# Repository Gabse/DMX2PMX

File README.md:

DMX2PMX
=
DMX512 to Dual PMX Converter

=
This simple device converts a standard DMX512 Signal into two Pulsar PMX signals.

It lets you reuse your old Pulsar/ClayPaky gear with almost any standard DMX controller on the market.

The device has 2 independent outputs giving the user the posibility to split the incomming signal into two outputs 
to achieve a faster update rate than by using a single PMX channel only (≈2,08ms per channel in 7 bit mode).

The number of desired channels per output and the bit mode can be modified in the sourcecode file.

9 Dip Swithes make it possible to set a DMX start address, in order to expand existing DMX universes.

The opto-isolated input helps to avoid ground loops between the DMX and the PMX side.

Please also visit my [Blog Post](https://gabsesblog.blogspot.com/2021/07/clay-packy-golden-scan.html) for additional information.

Safety information / disclaimer:
=

This device SHOULD NOT be used with anything safety related. It is only meant to control dimmer packs and other lighting fixtures.
It is not allowed to be used with moving stage parts, pyros and similar SFX. Doing so will happen at your OWN RISK!

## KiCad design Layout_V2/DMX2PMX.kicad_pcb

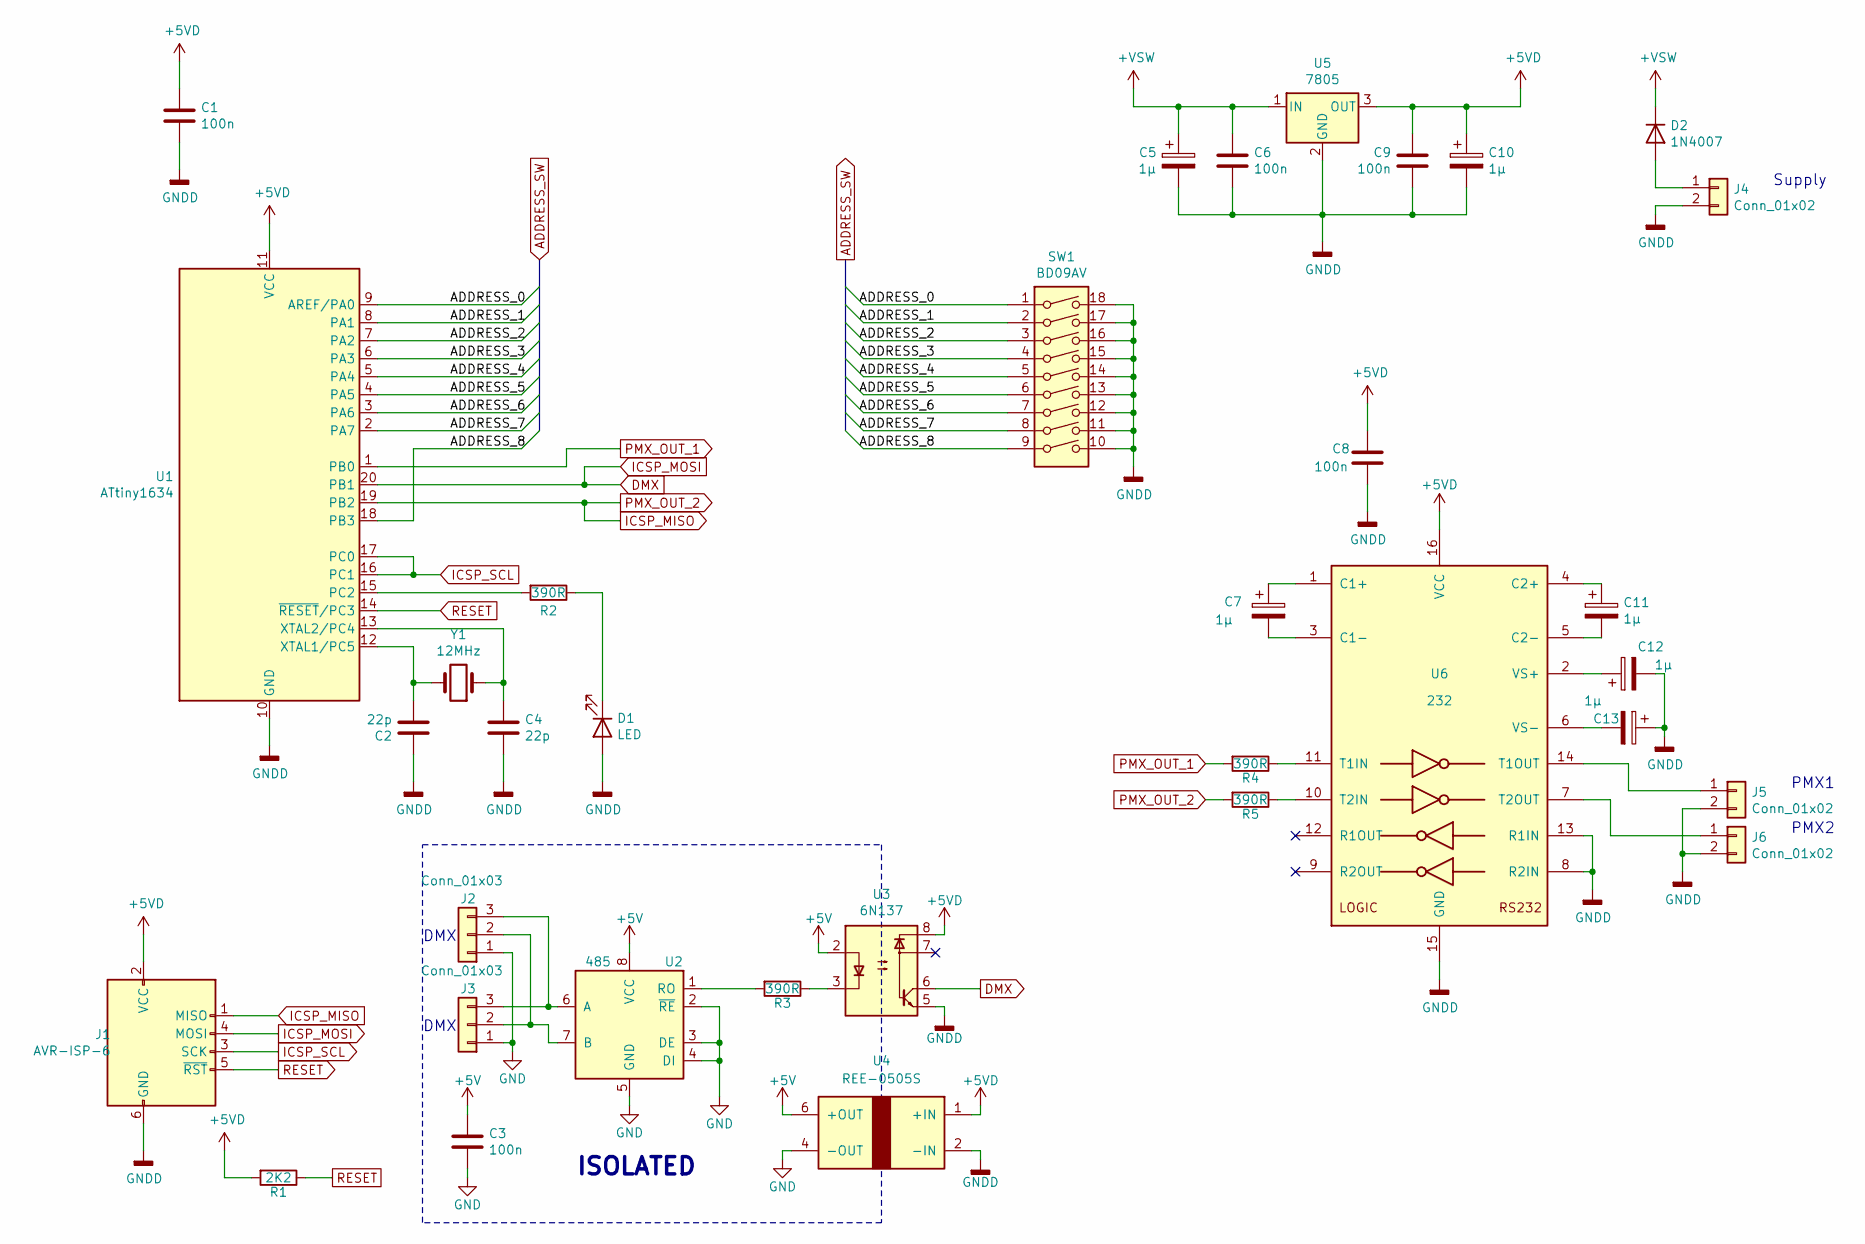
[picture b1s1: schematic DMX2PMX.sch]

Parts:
C1, C3, C6, C8, C9: 100n; C_Disc_D3.0mm_W1.6mm_P2.50mm; MPN C315C103K5R5TA
C2, C4: 22p; C_Disc_D3.0mm_W1.6mm_P2.50mm; MPN C315C229D2G5TA
C5, C7, C10, C11, C12, C13: 1µ; CP_Radial_D6.3mm_P2.50mm; MPN UPS2D010MED
D1: LED; LED_D5.0mm; MPN TLHY5400-AS12Z
D2: 1N4007; D_DO-15_P12.70mm_Horizontal; MPN 1N4007-E3/54
J1: AVR-ISP-6; PinHeader_2x03_P2.54mm_Vertical; MPN 67996-206HLF
J2, J3: Conn_01x03; PinHeader_1x03_P2.54mm_Vertical; MPN 90120-0763
J4, J5, J6: Conn_01x02; PinHeader_1x02_P2.54mm_Vertical; MPN 90120-0762
R1: 2K2; R_Axial_DIN0309_L9.0mm_D3.2mm_P12.70mm_Horizontal; MPN MBA02040C2201FCT00
R2, R3, R4, R5: 390R; R_Axial_DIN0309_L9.0mm_D3.2mm_P12.70mm_Horizontal; MPN MBA02040C3900FC100
SW1: BD09AV; MPN BD09AV
U1: ATtiny1634; SOIC-20W_7.5x12.8mm_Pitch1.27mm; MPN ATTINY1634-SU
U2: 485; DIP-8_W7.62mm_Socket_LongPads; MPN SN75176BP
U3: 6N137; DIP-8_W7.62mm_Socket_LongPads; MPN 6N137
U4: REE-0505S; RECOM-REE-0505S; MPN REE-0505S
U5: 7805; TO-220-3_Vertical; MPN L7805ABP
U6: 232; DIP-16_W7.62mm_Socket_LongPads; MPN MAX232N
Y1: 12MHz; Crystal_HC49-4H_Vertical; MPN LF XTAL003215

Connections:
+5V: C3.1, U2.8 (VCC), U3.2, U4.6 (+OUT)
+5VD: C1.1, C8.1, C9.1, C10.1, J1.2 (VCC), R1.2, U1.11 (VCC), U3.8, U4.1 (+IN), U5.3 (OUT), U6.16 (VCC)
+VSW: C5.1, C6.1, D2.1 (K), U5.1 (IN)
/ADDRESS_0: SW1.1, U1.9 (AREF/PA0)
/ADDRESS_1: SW1.2, U1.8 (PA1)
/ADDRESS_2: SW1.3, U1.7 (PA2)
/ADDRESS_3: SW1.4, U1.6 (PA3)
/ADDRESS_4: SW1.5, U1.5 (PA4)
/ADDRESS_5: SW1.6, U1.4 (PA5)
/ADDRESS_6: SW1.7, U1.3 (PA6)
/ADDRESS_7: SW1.8, U1.2 (PA7)
/ADDRESS_8: SW1.9, U1.18 (PB3)
DMX: J1.4 (MOSI), U1.20 (PB1), U3.6
GND: C3.2, J2.1, J3.1, U2.2 (~RE~), U2.3 (DE), U2.4 (DI), U2.5 (GND), U4.4 (-OUT)
GNDD: C1.2, C2.1, C4.2, C5.2, C6.2, C8.2, C9.2, C10.2, C12.2, C13.1, D1.2 (A), J1.6 (GND), J4.2, J5.2, J6.2, SW1.10, SW1.11, SW1.12, SW1.13, SW1.14, SW1.15, SW1.16, SW1.17, SW1.18, U1.10 (GND), U3.5, U4.2 (-IN), U5.2 (GND), U6.8 (R2IN), U6.13 (R1IN), U6.15 (GND)
ICSP_MISO: J1.1 (MISO), R5.2, U1.19 (PB2)
ICSP_SCL: J1.3 (SCK), U1.16 (PC1), U1.17 (PC0)
unnamed: C2.2, U1.12 (XTAL1/PC5), Y1.2
unnamed: C4.1, U1.13 (XTAL2/PC4), Y1.1
unnamed: C7.1, U6.1 (C1+)
unnamed: C7.2, U6.3 (C1-)
unnamed: C11.1, U6.4 (C2+)
unnamed: C11.2, U6.5 (C2-)
unnamed: C12.1, U6.2 (VS+)
unnamed: C13.2, U6.6 (VS-)
unnamed: D1.1 (K), R2.1
unnamed: D2.2 (A), J4.1
unnamed: J2.2, J3.2, U2.7 (B)
unnamed: J2.3, J3.3, U2.6 (A)
unnamed: J5.1, U6.14 (T1OUT)
unnamed: J6.1, U6.7 (T2OUT)
unnamed: R2.2, U1.15 (PC2)
unnamed: R3.1, U3.3
unnamed: R3.2, U2.1 (RO)
unnamed: R4.1, U6.11 (T1IN)
unnamed: R5.1, U6.10 (T2IN)
PMX_OUT_1: R4.2, U1.1 (PB0)
RESET: J1.5 (~RST), R1.1, U1.14 (~RESET~/PC3)

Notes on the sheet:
DMX
ISOLATED
PMX1
PMX2
Supply

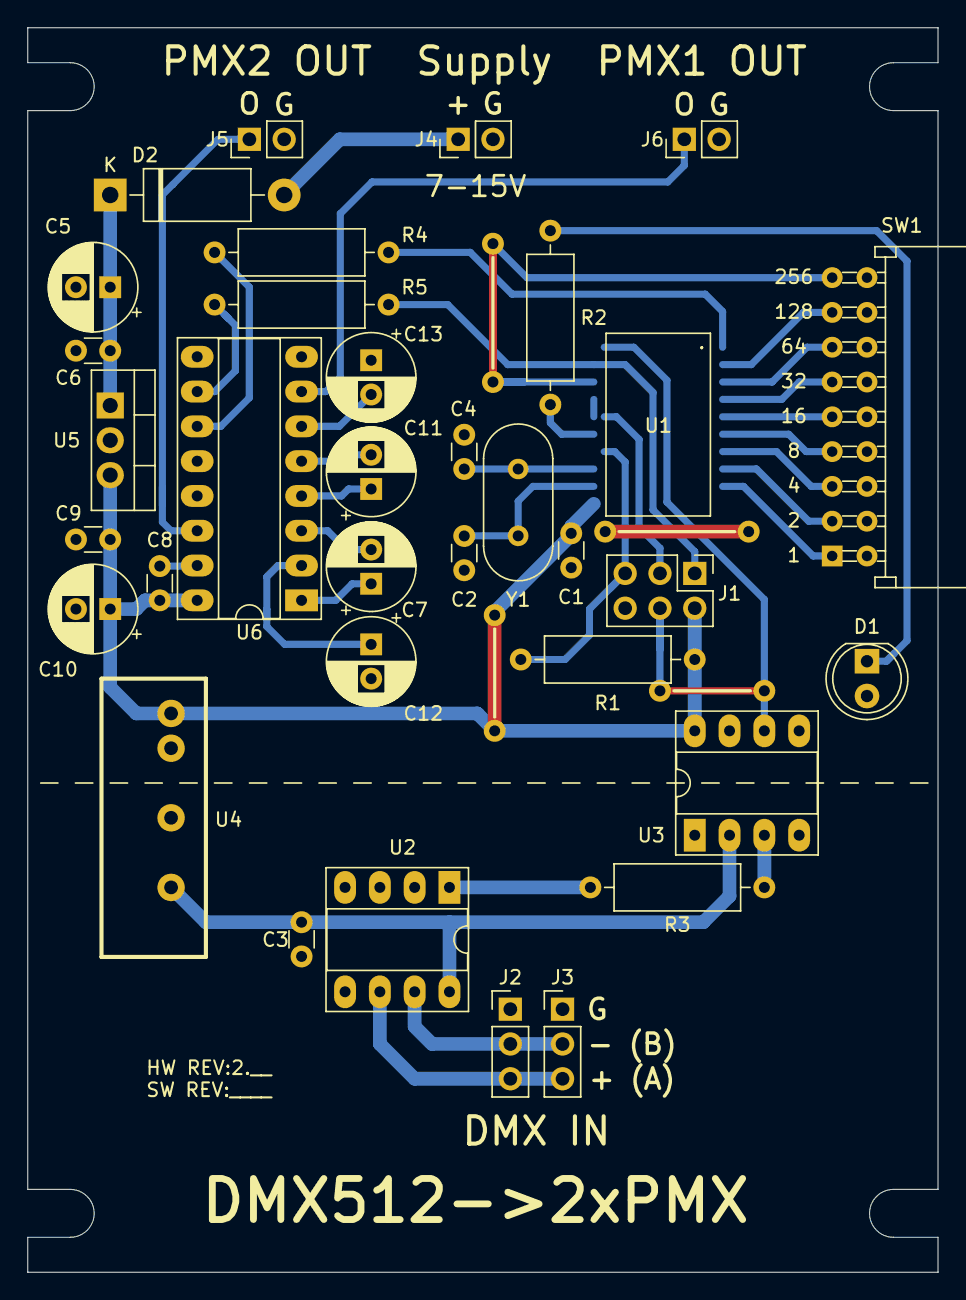
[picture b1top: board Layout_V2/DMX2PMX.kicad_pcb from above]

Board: 2 copper layers, 66.4 x 90.9 mm, 34 parts (1 on the bottom side), 38 nets.

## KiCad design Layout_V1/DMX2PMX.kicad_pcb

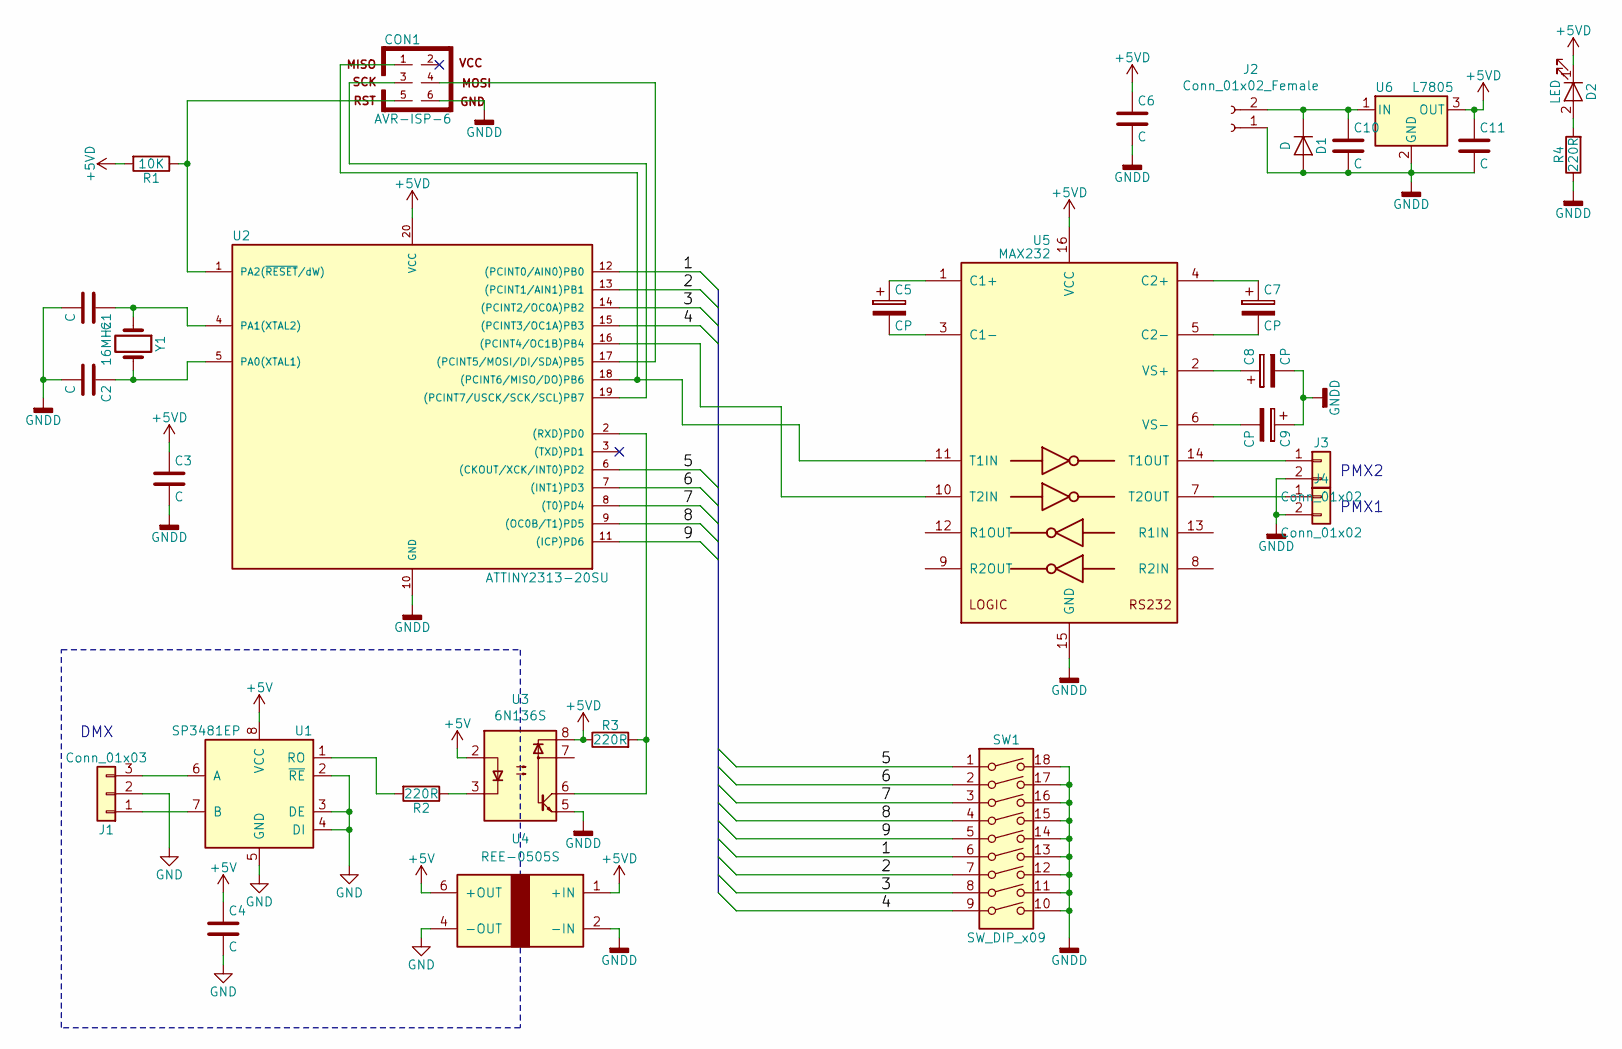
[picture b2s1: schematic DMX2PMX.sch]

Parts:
C1, C2, C3, C4, C6, C10, C11: C; C_Disc_D3.0mm_W1.6mm_P2.50mm
C5, C7, C8, C9: CP; CP_Radial_D5.0mm_P2.50mm
CON1: AVR-ISP-6; SDL-106-X-XX_2x03
D1: D; D_DO-41_SOD81_P12.70mm_Horizontal
D2: LED; LED_D5.0mm
J1: Conn_01x03; Socket_Strip_Straight_1x03_Pitch2.54mm
J2: Conn_01x02_Female; PhoenixContact_MSTB-GF_02x5.08mm_Angled_ThreadedFlange_Moun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
J3, J4: Conn_01x02; Socket_Strip_Straight_1x02_Pitch2.54mm
R1: 10K; R_Axial_DIN0309_L9.0mm_D3.2mm_P12.70mm_Horizontal
R2, R3, R4: 220R; R_Axial_DIN0309_L9.0mm_D3.2mm_P12.70mm_Horizontal
SW1: SW_DIP_x09; SW_DIP_x9_W7.62mm_Slide
U1: SP3481EP; DIP-8_W7.62mm_Socket_LongPads
U2: ATTINY2313-20SU; SOIC-20W_7.5x12.8mm_Pitch1.27mm
U3: 6N136S; DIP-8_W7.62mm_Socket_LongPads
U4: REE-0505S; RECOM-REE-0505S; MPN REE-0505S
U5: MAX232; DIP-16_W7.62mm_Socket_LongPads
U6: L7805; TO-220
Y1: 16MHz; Crystal_HC49-U_Vertical

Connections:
+5V: C4.1, U1.8 (VCC), U3.2, U4.6 (+OUT)
+5VD: C3.1, C6.1, C11.1, D2.1 (K), R1.2, R3.1, U2.20 (VCC), U3.8, U4.1 (+IN), U5.16 (VCC), U6.3 (OUT)
/1: SW1.6, U2.12 ((PCINT0/AIN0)PB0)
/2: SW1.7, U2.13 ((PCINT1/AIN1)PB1)
/3: SW1.8, U2.14 ((PCINT2/OC0A)PB2)
/4: SW1.9, U2.15 ((PCINT3/OC1A)PB3)
/5: SW1.1, U2.6 ((CKOUT/XCK/INT0)PD2)
/6: SW1.2, U2.7 ((INT1)PD3)
/7: SW1.3, U2.8 ((T0)PD4)
/8: SW1.4, U2.9 ((OC0B/T1)PD5)
/9: SW1.5, U2.11 ((ICP)PD6)
GND: C4.2, J1.2, U1.2 (~RE~), U1.3 (DE), U1.4 (DI), U1.5 (GND), U4.4 (-OUT)
GNDD: C1.2, C2.2, C3.2, C6.2, C8.2, C9.1, C10.2, C11.2, CON1.6, D1.2 (A), J2.1, J3.2, J4.2, R4.1, SW1.10, SW1.11, SW1.12, SW1.13, SW1.14, SW1.15, SW1.16, SW1.17, SW1.18, U2.10 (GND), U3.5, U4.2 (-IN), U5.15 (GND), U6.2 (GND)
unnamed: C1.1, U2.4 (PA1(XTAL2)), Y1.1
unnamed: C2.1, U2.5 (PA0(XTAL1)), Y1.2
unnamed: C5.1, U5.1 (C1+)
unnamed: C5.2, U5.3 (C1-)
unnamed: C7.1, U5.4 (C2+)
unnamed: C7.2, U5.5 (C2-)
unnamed: C8.1, U5.2 (VS+)
unnamed: C9.2, U5.6 (VS-)
unnamed: C10.1, D1.1 (K), J2.2, U6.1 (IN)
unnamed: CON1.1, U2.18 ((PCINT6/MISO/DO)PB6), U5.11 (T1IN)
unnamed: CON1.3, U2.19 ((PCINT7/USCK/SCK/SCL)PB7)
unnamed: CON1.4, U2.17 ((PCINT5/MOSI/DI/SDA)PB5)
unnamed: CON1.5, R1.1, U2.1 (PA2(~RESET~/dW))
unnamed: D2.2 (A), R4.2
unnamed: J1.1, U1.7 (B)
unnamed: J1.3, U1.6 (A)
unnamed: J3.1, U5.14 (T1OUT)
unnamed: J4.1, U5.7 (T2OUT)
unnamed: R2.1, U3.3
unnamed: R2.2, U1.1 (RO)
unnamed: R3.2, U2.2 ((RXD)PD0), U3.6
unnamed: U2.16 ((PCINT4/OC1B)PB4), U5.10 (T2IN)

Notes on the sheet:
PMX2
DMX
PMX1

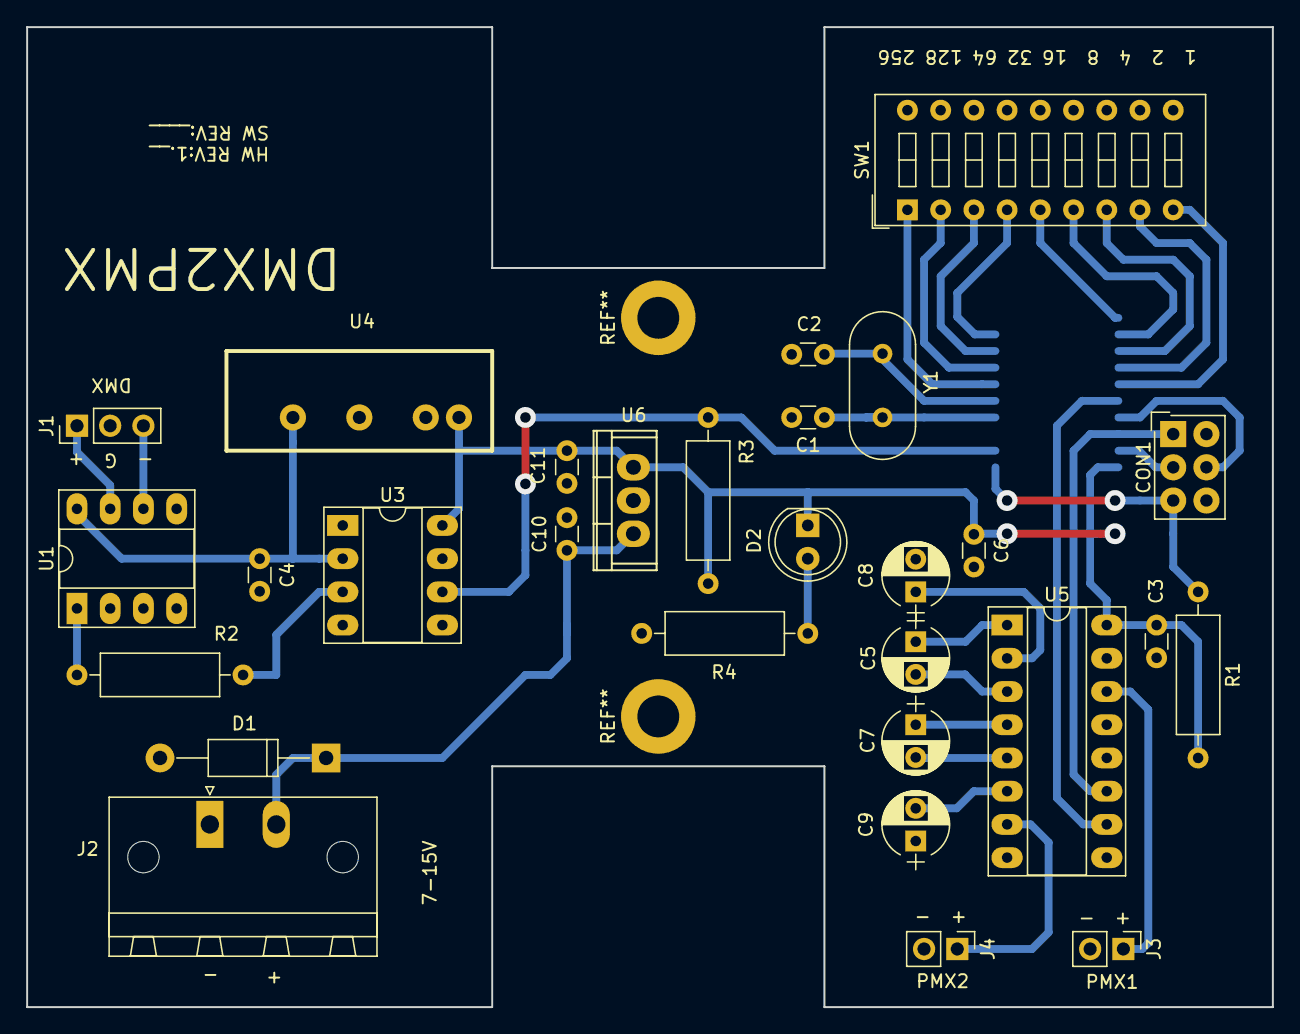
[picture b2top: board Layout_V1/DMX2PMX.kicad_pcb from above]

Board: 2 copper layers, 95.2 x 74.9 mm, 30 parts (1 on the bottom side), 35 nets.

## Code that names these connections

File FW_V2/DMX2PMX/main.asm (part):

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//
//	Attiny Pinout:
//					ADDRESS SW = 0-7= PORTA
//					PMX1	= UART0	= PB0
//					DMX		= UART1 = PB1
//					PMX2	= USI	= PB2
//					ADDRESS SW	= 8	= PB3
//					PMX CLOCK	= PC0&PC1
//					LED		= LED	= PC2
//
//	Fuse Settings: 
//						EXTENDED:	0xF5
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
//******************************General FLAGS*******************************

.equ DSNB			=	0						// DMX Skip Next Byte
.equ DRSB			=	1						// DMX Read Start Byte
.equ LEDT			=	2						// LED Toggle
.equ USIS			=	3						// USI State

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
//*****************************Init USI for PMX2****************************
	
	LDI TEMP,	1<<USIOIE | 1<<USIWM0 | 1<<USICS1// Set USI to 3Wire mode, clock from PC1 & interrupt on USI overflow
	OUT USICR,	TEMP							// Set USI to 3Wire mode, clock from PC1 & interrupt on USI overflow
	SER TEMP									// Set USI output to 1
	OUT USIDR,	TEMP							// Set USI output to 1
	LDI TEMP,	1<<USIOIF | 8					// Reset USI Overflow Flag & Set USI Counter to 8 offsetting the PMX Interrupts against each other
	OUT USISR,	TEMP							// Reset USI Overflow Flag & Set USI Counter to 8 offsetting the PMX Interrupts against each other
	SBI DDRB,	PB2								// Set PMX2 pin to output
	LDI TEMP,	NUM_CH							// Load number of channels into TEMP
	MOV PMX2_LAST,	TEMP						// Copy number of channels into PMX2_LAST

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	OUT UBRR0H, TEMP							// Set USART 0 baud register MSB to 9600Hz
	LDI TEMP,	LOW ((F_CPU/(9600*2))-1)		// Set USART 0 baud register LSB to 9600Hz
	OUT UBRR0L, TEMP							// Set USART 0 baud register LSB to 9600Hz
	SBI DDRC,	PC0								// Enable clock output
	

//****************************Init USART1 for DMX***************************
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	STS UBRR1H, TEMP							// Set USART 1 baud register MSB to 250kHz
	LDI TEMP,	LOW ((F_CPU/(250000*16))-1)		// Set USART 1 baud register LSB to 250kHz
	STS UBRR1L, TEMP							// Set USART 1 baud register LSB to 250kHz
	SBI PUEB,	PB1								// Enable DMX pullup


//******************************Init Timer for LED**************************
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	STS TCCR1A, TEMP							// Reset Timer/Counter1 Control Register A
	LDI TEMP,	1<<WGM12 | 1<<CS10 | 1<<CS12	// Set Timer/Counter1 Control Register B to Clear Timer on Compare A & Clock/1024
	STS TCCR1B, TEMP							// Set Timer/Counter1 Control Register B to Clear Timer on Compare A & Clock/1024
	SBI DDRC,	PC2								// Set LED pin to output
	SBI PORTC,	PC2								// Turn LED ON


//******************************General Init********************************
	
	LDI TEMP,	1<<WDE							// Enable Watchdog Timer @ 16ms
	OUT WDTCSR,	TEMP							// Enable Watchdog Timer @ 16ms
	CBI DDRB,	PB3								// Set pin PB3 to input
	SBI PUEB,	PB3								// Enable pin PB3 pullup
	LDI TEMP,	0x00							// Set PortA to input 
	OUT DDRA,	TEMP							// Set PortA to input 
	LDI TEMP,	0xFF							// Enable PortA pullup
	OUT PUEA,	TEMP							// Enable PortA pullup
	SER TEMP									// Load TEMP with value for XOR
	IN DMX_ADDRESS_L,	PINB					// Read DMX address bit 8 from DIP switch
	EOR DMX_ADDRESS_L,	TEMP					// Invert register
	BST DMX_ADDRESS_L,	PB3						// Copy DMX address PB3 to T
	BLD DMX_ADDRESS_H,	0						// Copy T to DMX_ADDRESS_H bit 0
	IN DMX_ADDRESS_L,	PINA					// Read DMX address bit 0-7 from DIP switch
	EOR DMX_ADDRESS_L,	TEMP					// Invert register
	LDI XH,	0x02								// Set Main address MSB to 2
	LDI YH, 0x01								// Set PMX address MSB to 1
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	CONTINUE:
		// Check if DIP switch address has changed, and force a device reset by not reseting the watchdog if address has changed.
		SER TEMP								// Load TEMP with value for XOR
		IN DMX_ADDRESS_L_C,	PINB				// Read DMX address bit 8 from DIP switch
		EOR DMX_ADDRESS_L_C,	TEMP			// Invert register
		BST DMX_ADDRESS_L_C,	PB3				// Copy DMX address PB3 to T
		BLD DMX_ADDRESS_H_C,	0				// Copy T to DMX_ADDRESS_H_C bit 0
		IN DMX_ADDRESS_L_C,	PINA				// Read DMX address bit 0-7 from DIP switch
		EOR DMX_ADDRESS_L_C,	TEMP			// Invert register
		CPSE DMX_ADDRESS_L_C,	DMX_ADDRESS_L	// Compare new address LSB with set address
			RJMP loop								// Jump back to loop if address LSB has changed, forcing a device reset
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	
		// Check if DMX has updated since the last Interrupt, and flash the LED if update has ocoured. Turn the LED ON otherwise.	
		IN S_SREG,	SREG						// Save SREG
		SBI PINC,	PC2							// Toggle LED
		SBRS FLAGS,	LEDT						// Check DMX status for LED toggle
			SBI PORTC, PC2							// Turn LED ON
		CBR FLAGS,	1<<LEDT						// Clear LEDT flag
		OUT SREG,	S_SREG						// Restore SREG
		RETI									// Exit interrupt
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		CBR FLAGS,	1<<USIS							// Reset USI state flag
		OUT USIDR,	USI_DAT							// Output USI_DAT to USIDR
		LDI USI_DAT,	1<<USIOIF | 8				// Reset USI Overflow Flag & Set USI Counter to 8
		SBIS PINC,	PC1								// Check clock phase
			LDI USI_DAT,	1<<USIOIF | 9				// Correct clock phase (Interrupt on rising edge, output on falling edge)
		OUT USISR,	USI_DAT							// Reset USI Overflow Flag & Set USI Counter to 8/9
		OUT SREG,	S_SREG							// Restore SREG
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
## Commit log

2022-07-24 Fix random reboot, fix OBOE
    Fix MCU randomly rebooting.
    Fix DMX address DIP switch off-by-one-error.

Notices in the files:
FW_V2/DMX2PMX/main.asm:
Licence: CC BY-NC-SA
Layout_V2/DMX2PMX.kicad_pcb:
CC BY-NC-SA
